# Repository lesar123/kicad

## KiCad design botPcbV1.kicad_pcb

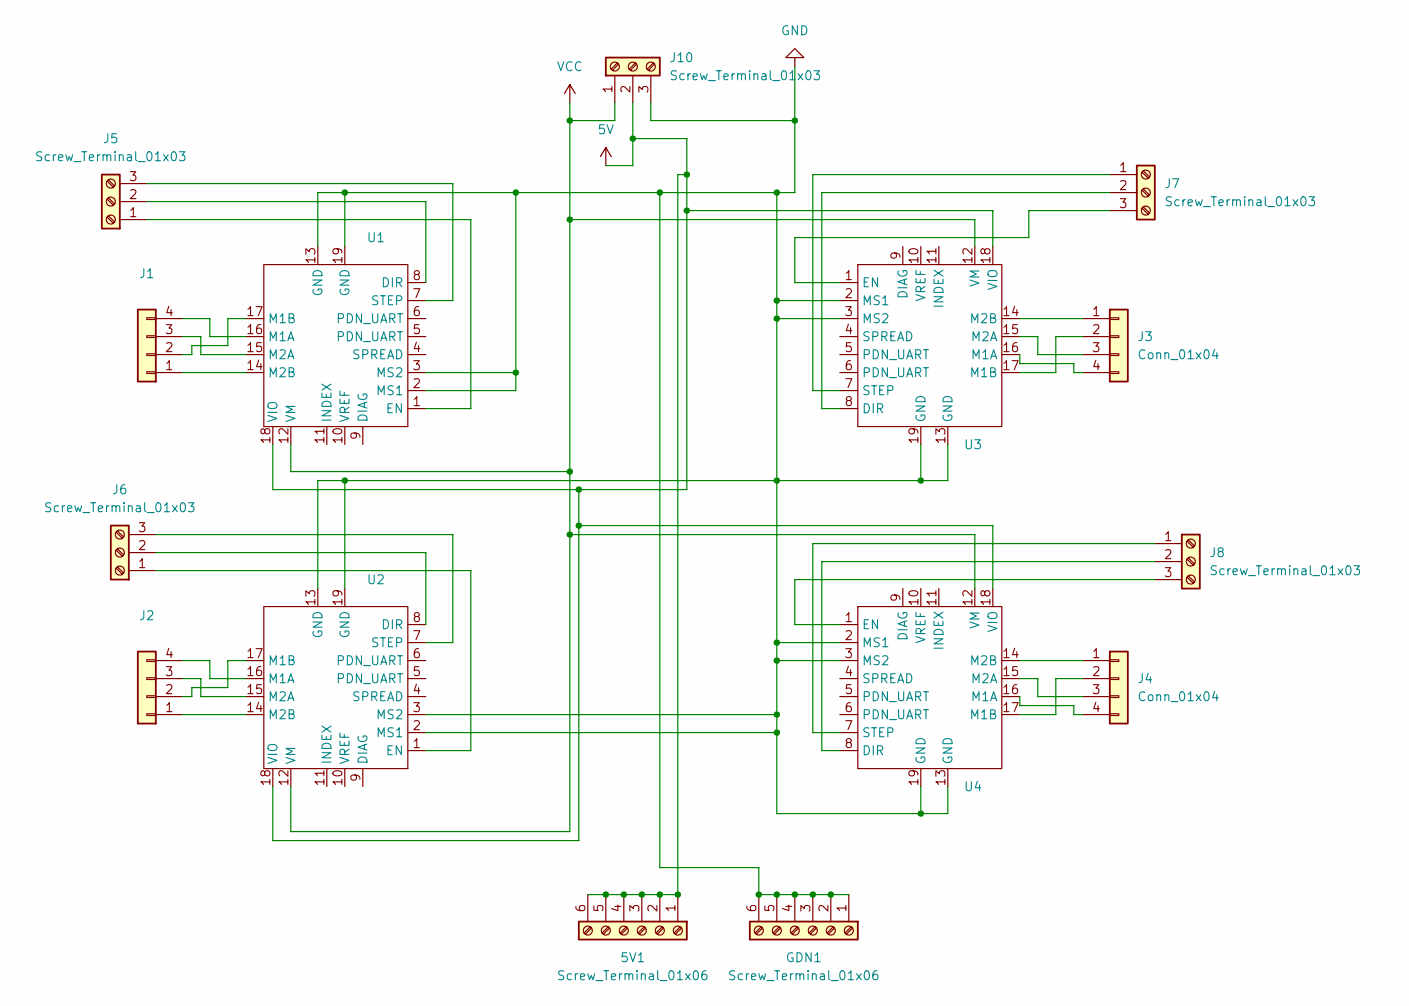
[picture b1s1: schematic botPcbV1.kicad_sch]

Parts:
5V1: Screw_Terminal_01x06; TerminalBlock_4Ucon_1x06_P3.50mm_Horizontal
GDN1: Screw_Terminal_01x06; TerminalBlock_4Ucon_1x06_P3.50mm_Horizontal
J1, J2, J3, J4: Conn_01x04; PinHeader_1x04_P2.54mm_Vertical
J5, J6, J7, J8, J10: Screw_Terminal_01x03; TerminalBlock_4Ucon_1x03_P3.50mm_Horizontal
U1, U2, U3, U4: MODULE_TMC2209_SILENTSTEPSTICK

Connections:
5V: 5V1.1, 5V1.2, 5V1.3, 5V1.4, 5V1.5, 5V1.6, J10.2, U1.18 (VIO), U2.18 (VIO), U3.18 (VIO), U4.18 (VIO)
GND: GDN1.1, GDN1.2, GDN1.3, GDN1.4, GDN1.5, GDN1.6, J10.3, U1.2 (MS1), U1.3 (MS2), U1.13 (GND), U1.19 (GND), U2.2 (MS1), U2.3 (MS2), U2.13 (GND), U2.19 (GND), U3.2 (MS1), U3.3 (MS2), U3.13 (GND), U3.19 (STEP), U4.2 (MS1), U4.3 (MS2), U4.13 (GND), U4.19 (STEP)
unnamed: J1.1, U1.14 (M2B)
unnamed: J1.2, U1.17 (M1B)
unnamed: J1.3, U1.15 (M2A)
unnamed: J1.4, U1.16 (M1A)
unnamed: J2.1, U2.14 (M2B)
unnamed: J2.2, U2.17 (M1B)
unnamed: J2.3, U2.15 (M2A)
unnamed: J2.4, U2.16 (M1A)
unnamed: J3.1, U3.14 (M2B)
unnamed: J3.2, U3.17 (M1B)
unnamed: J3.3, U3.15 (M2A)
unnamed: J3.4, U3.16 (M1A)
unnamed: J4.1, U4.14 (M2B)
unnamed: J4.2, U4.17 (M1B)
unnamed: J4.3, U4.15 (M2A)
unnamed: J4.4, U4.16 (M1A)
unnamed: J5.1, U1.1 (EN)
unnamed: J5.2, U1.8 (DIR)
unnamed: J5.3, U1.7 (STEP)
unnamed: J6.1, U2.1 (EN)
unnamed: J6.2, U2.8 (DIR)
unnamed: J6.3, U2.7 (STEP)
unnamed: J7.1, U3.7 (STEP)
unnamed: J7.2, U3.8 (DIR)
unnamed: J7.3, U3.1 (EN)
unnamed: J8.1, U4.7 (STEP)
unnamed: J8.2, U4.8 (DIR)
unnamed: J8.3, U4.1 (EN)
VCC: J10.1, U1.12 (VM), U2.12 (VM), U3.12 (VM), U4.12 (VM)

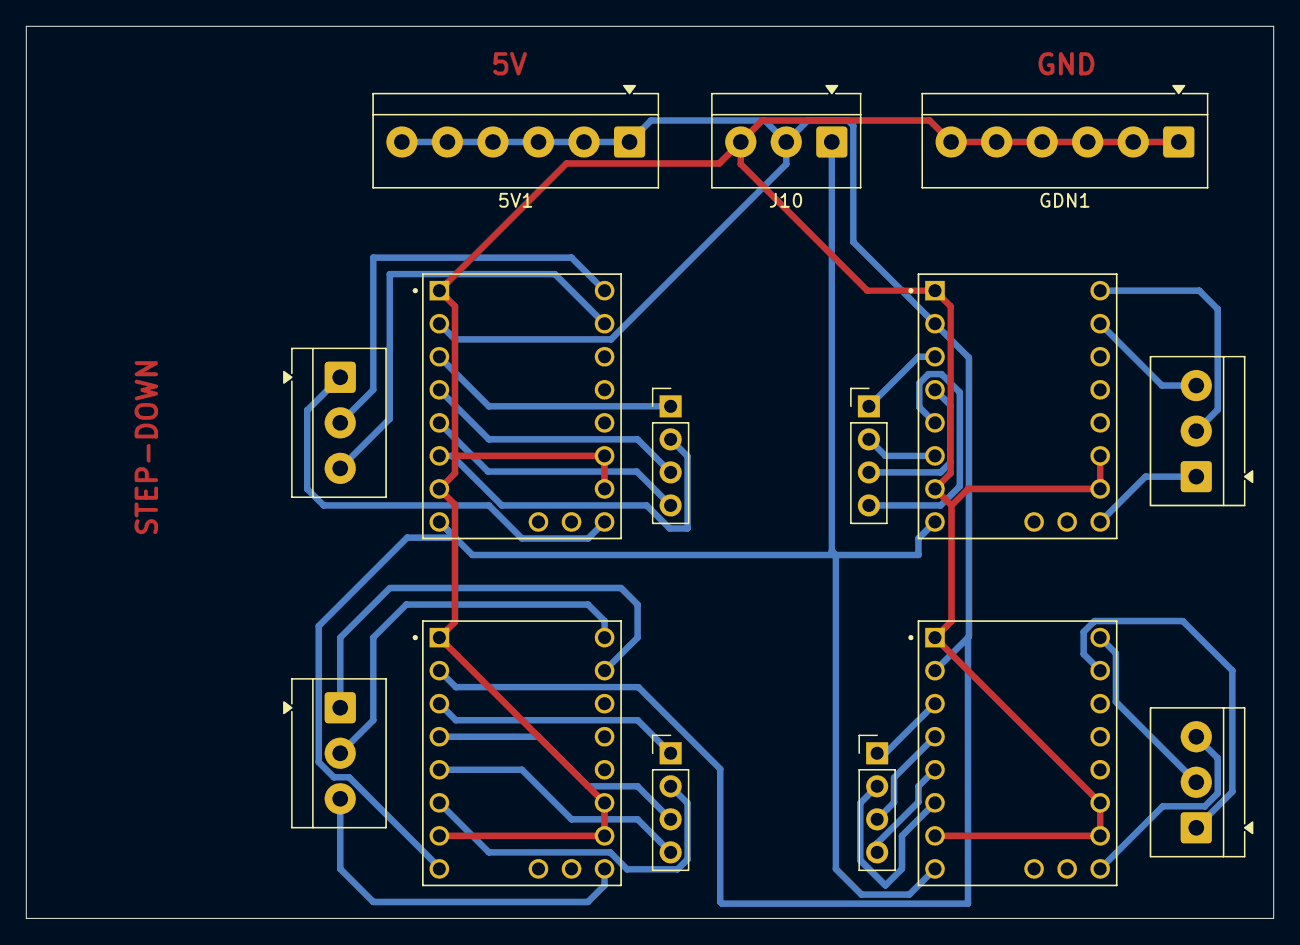
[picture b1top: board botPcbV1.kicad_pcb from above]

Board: 2 copper layers, 95.9 x 68.6 mm, 15 parts (0 on the bottom side), 31 nets.

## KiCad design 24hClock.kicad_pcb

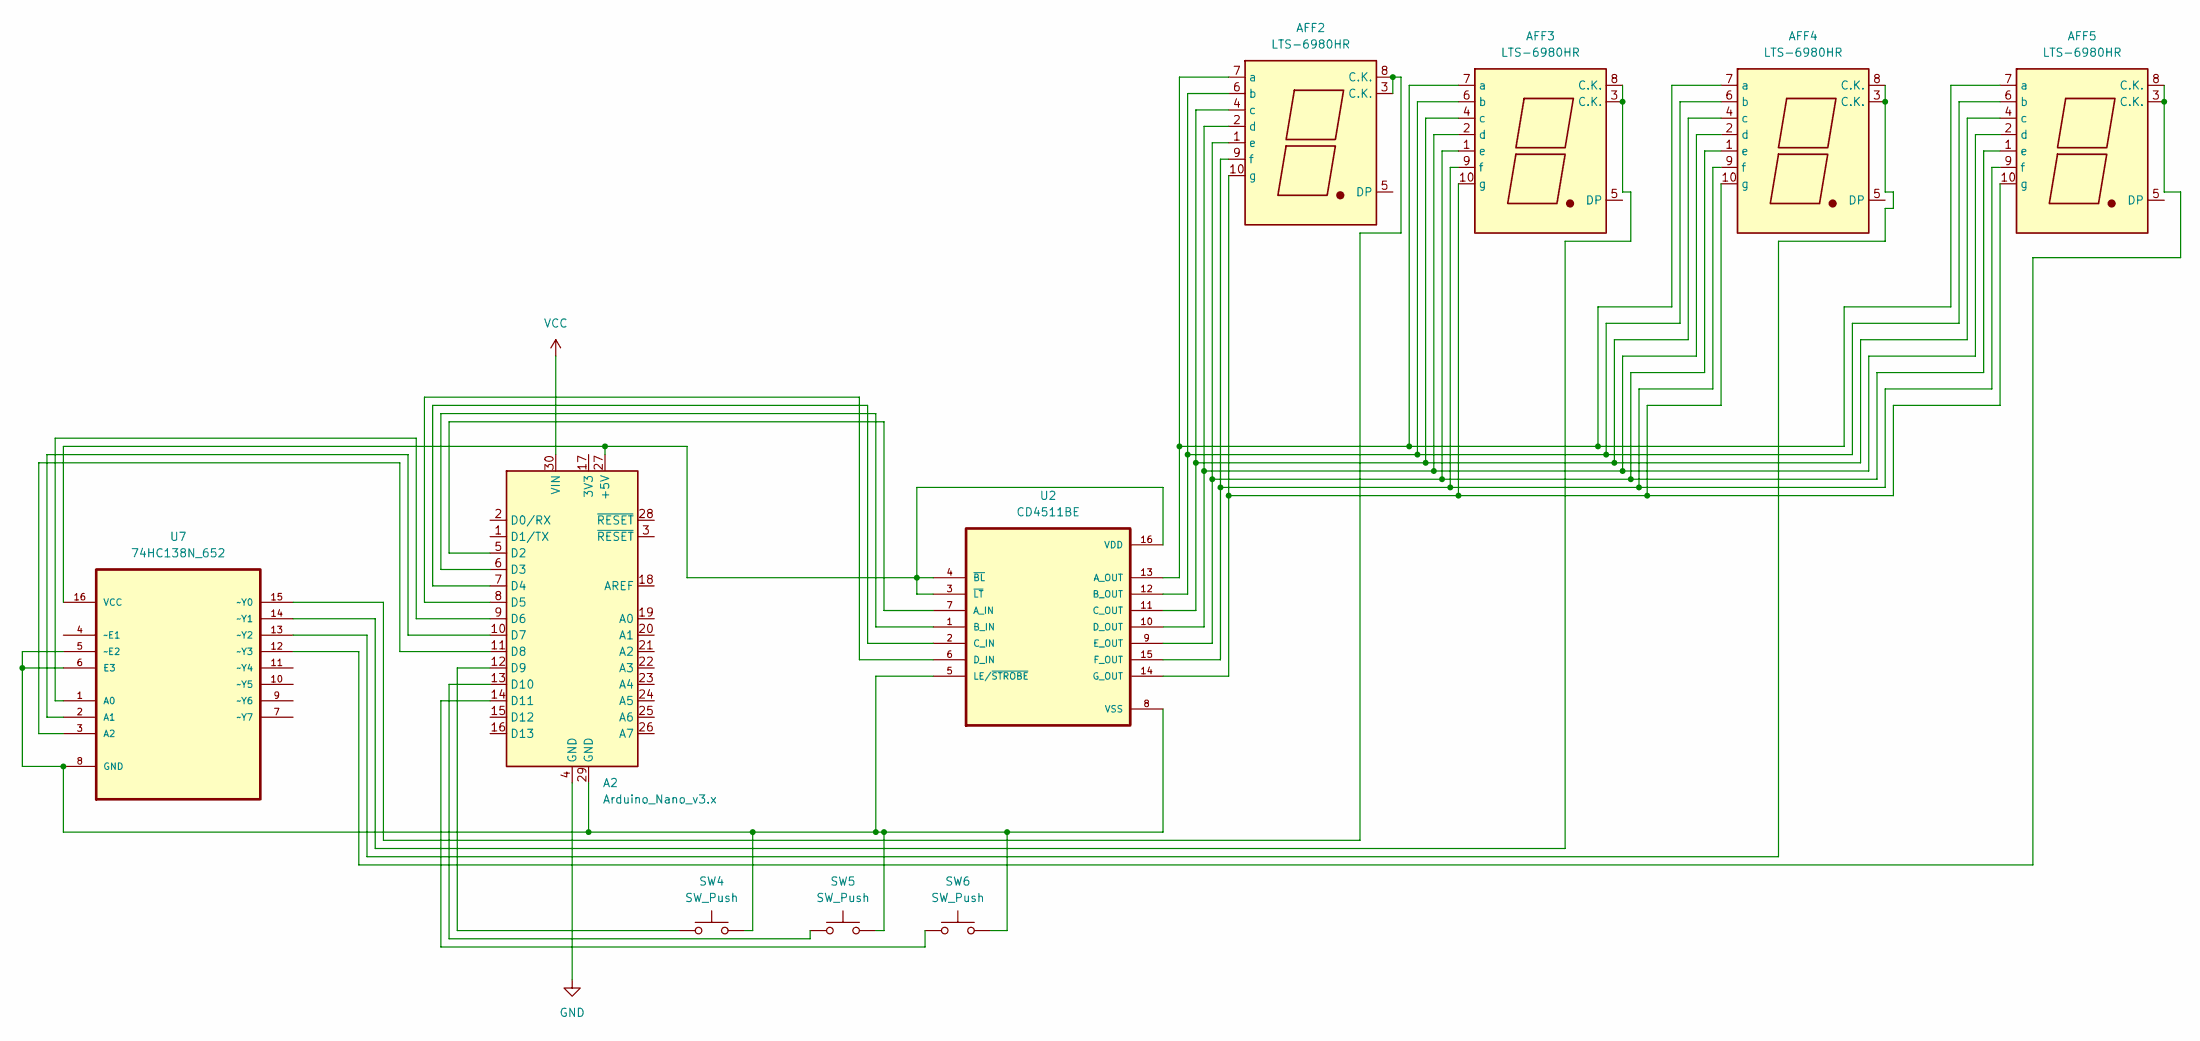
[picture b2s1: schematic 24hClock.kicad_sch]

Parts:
A2: Arduino_Nano_v3.x; Arduino_Nano
AFF2, AFF3, AFF4, AFF5: LTS-6980HR; 7SegmentLED_LTS6760_LTS6780
SW4, SW5, SW6: SW_Push; SW_PUSH_6mm_H5mm
U2: CD4511BE; DIP794W45P254L1969H508Q16
U7: 74HC138N_652; DIP254P762X470-16; MPN 74HC138N,652

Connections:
GND: A2.4 (GND)
unnamed: A2.27 (+5V), U2.3 (~LT), U2.4 (~BL), U2.16 (VDD), U7.16 (VCC)
unnamed: A2.5 (D2), U2.7 (A_IN)
unnamed: A2.6 (D3), U2.1 (B_IN)
unnamed: A2.7 (D4), U2.2 (C_IN)
unnamed: A2.8 (D5), U2.6 (D_IN)
unnamed: A2.9 (D6), U7.1 (A0)
unnamed: A2.10 (D7), U7.2 (A1)
unnamed: A2.11 (D8), U7.3 (A2)
unnamed: A2.12 (D9), SW4.1
unnamed: A2.13 (D10), SW5.1
unnamed: A2.14 (D11), SW6.1
unnamed: AFF2.7 (a), AFF3.7 (a), AFF4.7 (a), AFF5.7 (a), U2.13 (A_OUT)
unnamed: AFF2.6 (b), AFF3.6 (b), AFF4.6 (b), AFF5.6 (b), U2.12 (B_OUT)
unnamed: AFF2.4 (c), AFF3.4 (c), AFF4.4 (c), AFF5.4 (c), U2.11 (C_OUT)
unnamed: AFF2.2 (d), AFF3.2 (d), AFF4.2 (d), AFF5.2 (d), U2.10 (D_OUT)
unnamed: AFF2.1 (e), AFF3.1 (e), AFF4.1 (e), AFF5.1 (e), U2.9 (E_OUT)
unnamed: AFF2.9 (f), AFF3.9 (f), AFF4.9 (f), AFF5.9 (f), U2.15 (F_OUT)
unnamed: AFF2.10 (g), AFF3.10 (g), AFF4.10 (g), AFF5.10 (g), U2.14 (G_OUT)
unnamed: AFF2.3 (C.K.), AFF2.8 (C.K.), U7.15 (~Y0)
unnamed: AFF3.3 (C.K.), AFF3.8 (C.K.), U7.14 (~Y1)
unnamed: AFF4.3 (C.K.), AFF4.8 (C.K.), U7.13 (~Y2)
unnamed: AFF5.3 (C.K.), AFF5.8 (C.K.), U7.12 (~Y3)
VCC: A2.30 (VIN)

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
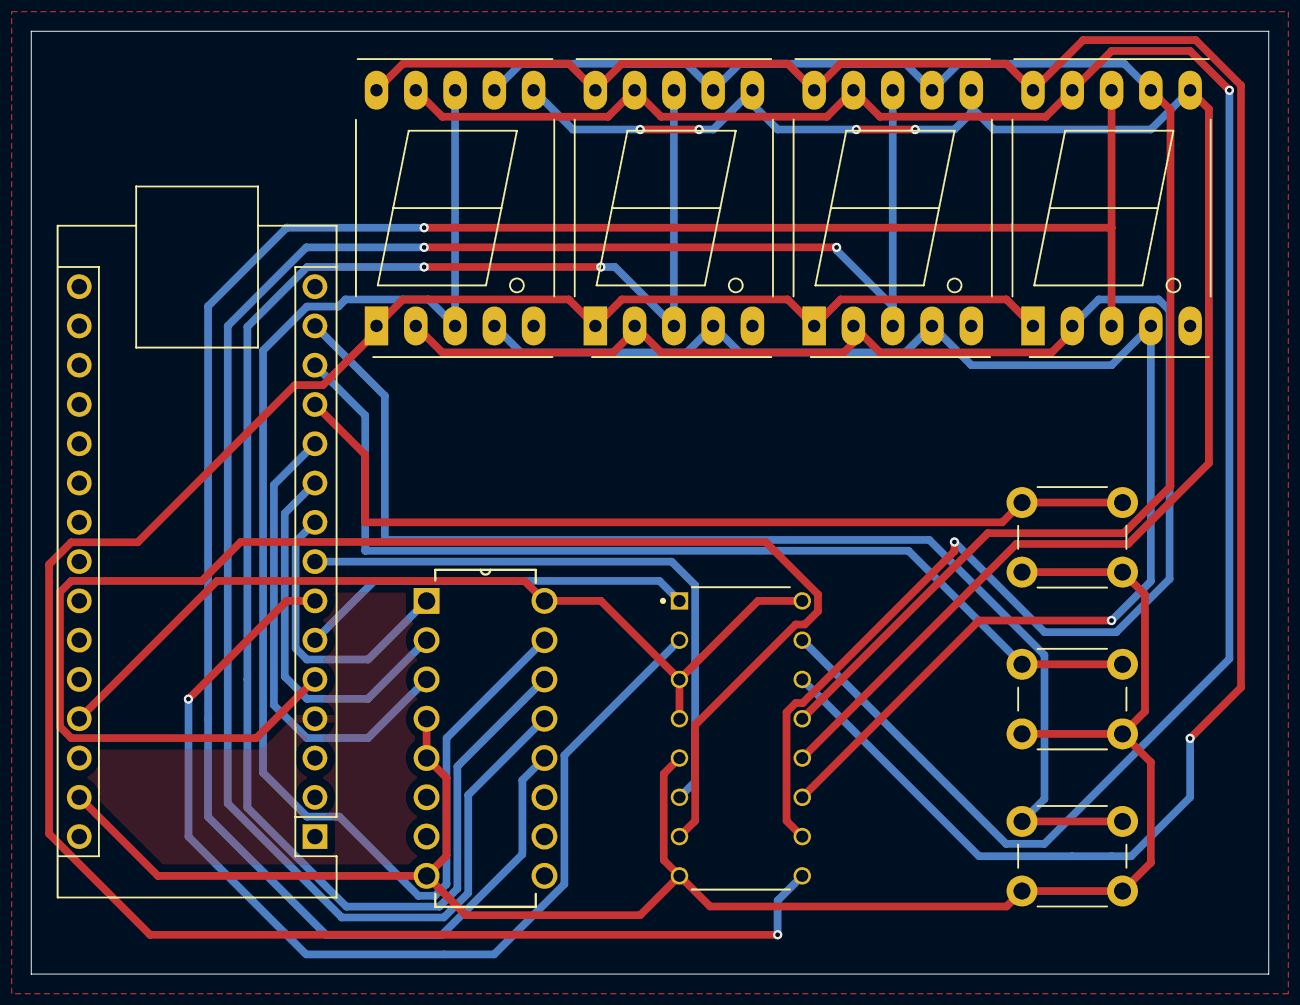
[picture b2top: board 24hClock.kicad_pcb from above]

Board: 2 copper layers, 80.0 x 61.0 mm, 10 parts (0 on the bottom side), 23 nets.
